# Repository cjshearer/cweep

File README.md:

## Overview

A compact, 34 key, solar powered, reversible, split keyboard.

<details>
  <summary>
    Schematic
  </summary>

</details>

## Case

The case is generated from `cweep.py` using CadQuery, with geometry extracted from user layers in `cweep.kicad_pcb`.

Generate case files to `case/`:

```sh
nix develop .#case --command python ~/repos/cweep/cweep.py
```

For interactive 3D viewing with live reloads:

```sh
nix develop .#case --command python ~/repos/cweep/cweep-dev.py
```

Changes to `cweep.py` or `cweep.kicad_pcb` automatically reload in the browser.

## Firmware

[*Generated by Shield Wizard for ZMK*](https://shield-wizard.genteure.workers.dev)

Reproducible builds with [Nix](https://nixos.org) thanks to [lilyinstarlight/zmk-nix](https://github.com/lilyinstarlight/zmk-nix):

```sh
# flash firmware with xiao dongle, resetting each board first
nix run .#flash reset reset reset dongle left right

# flash firmware with left as central, resetting each board first
nix run .#flash reset reset left_central right

# build all firmware and flash it yourself
nix build .#firmware
```

Builds in GitHub Actions coming soon.

## Bill of Materials (BOM)

| Description | Count | Value | Source |
|-------------|-------|-------|--------|
| Controller | 2 | [Seeed Xiao nRF52840](https://files.seeedstudio.com/wiki/XIAO/Seeed-Studio-XIAO-Series-SOM-Datasheet.pdf) | [Octopart](https://octopart.com/102010448-seeed+studio-126049022) |
| Controller Sockets | 4 | [310-43-107-41-001000](https://datasheet.octopart.com/310-43-107-41-001000-Mill-Max-datasheet-180673429.pdf) | [Octopart](https://octopart.com/310-43-107-41-001000-mill-max-657030) |
| Controller Pins | 28 | [3320-0-00-15-00-00-03-0](https://datasheet.octopart.com/3320-0-00-15-00-00-03-0-Mill-Max-datasheet-180682269.pdf) | [Octopart](https://octopart.com/3320-0-00-15-00-00-03-0-mill-max-29613931) |
| Battery/Reset Pogo Pins | 4 | [0906-0-15-20-76-14-11-0](https://datasheet.octopart.com/0906-0-15-20-76-14-11-0-Mill-Max-datasheet-180665642.pdf) | [Octopart](https://octopart.com/0906-0-15-20-76-14-11-0-mill-max-259418) |
| Battery | 2 | [ICR10440](https://www.powerstream.com/p/ICR10440-300mAh.pdf) | [Amazon](https://www.amazon.com/dp/B08H4RC1Y5) |
| Battery Contacts | 4 | [Keystone 230-1](https://docs.rs-online.com/a10d/0900766b8106e5ee.pdf) | [Octopart](https://octopart.com/230-1-keystone-154879) |
| Power Switch | 2 | [KAN-15](https://hackaday.io/project/174738-kan-15-led-tactile-switch/log/183418-switches-switches-switches#KAN-15:~:text=8016717020588253%26productId%3D4000960302909-,KAN%2D15,-Finally%2C%20I%20found) | [Amazon](https://us.amazon.com/dp/B0BHH2FBQ5) |
| Reset Button | 2 | [B3F-1020](https://omronfs.omron.com/en_US/ecb/products/pdf/en-b3f.pdf) (adafruit 367) | [Octopart](https://octopart.com/b3f-1020-omron-46944) |
| Kailh Choc V1 Keycaps | 34 | DDC Choc PBT Blanks | [Keebd](https://keebd.com/products/ddc-choc-pbt-blank-keycaps?variant=43210242785432) |
| Kailh Choc V1 Switches | 34 | [PG1350](https://cdn-shop.adafruit.com/product-files/5113/CHOC+keyswitch_Kailh-CPG135001D01_C400229.pdf) (e.g. [Sunset](https://cdn.shopify.com/s/files/1/0523/0847/6068/files/Choc_Sunset_datasheet.pdf))  | [Keebd](https://keebd.com/products/sunset-tactile-choc-switches?variant=41676091981976) |
| Kailh Choc Hotswap Sockets | 34 | [A5118](https://cdn-shop.adafruit.com/product-files/5118/5118-Choc-Socket.pdf) | [Octopart](https://octopart.com/5118-adafruit+industries-119967299) |
| Diodes | 34 | [1N4148W](https://datasheet.octopart.com/1N4148W-Diotec-datasheet-178941572.pdf) | [Octopart](https://octopart.com/1n4148w-diotec-42312312) |
| Solar Cell | 2 | [SM141K04LV](https://waf-e.dubudisk.com/anysolar.dubuplus.com/techsupport@anysolar.biz/O18Ae0B/DubuDisk/www/Gen3/SM141K04LV%20DATA%20SHEET%20202007.pdf) | [Octopart](https://octopart.com/sm141k04lv-anysolar-120091681) |
| Boost Converter | 2 | [BQ25504](https://www.ti.com/document-viewer/bq25504/datasheet) | [Octopart](https://octopart.com/bq25504rgtr-texas+instruments-20530455) |
| 4.7μF Capacitor (CHV1, CSTOR1) | 4 | [CL10A475KP8NNNC](https://datasheet.octopart.com/CL10A475KP8NNNC-Samsung-Electro-Mechanics-datasheet-11791968.pdf) | [Octopart](https://octopart.com/cl10a475kp8nnnc-samsung+electro-mechanics-9301844) |
| 10nF Capacitor (CREF1, CBYP1) | 4 | [C0603C103K5RACTU](https://octopart.com/c0603c103k5ractu-kemet-133094) | [Octopart](https://datasheet.octopart.com/C0603C103K5RACTU-Kemet-datasheet-11898999.pdf) |
| 22μH Inductor (LBST1) | 2 | [ASPI-4030S-220M-T](https://datasheet.octopart.com/ASPI-4030S-220M-T-Abracon-datasheet-27893147.pdf) | [Octopart](https://octopart.com/aspi-4030s-220m-t-abracon-29811505) |
| 4.42MΩ Resistor (ROV1) | 2 | [CRCW06034M42FKEA](https://datasheet.octopart.com/CRCW06034M42FKEA-Vishay-datasheet-175423584.pdf) | [Octopart](https://octopart.com/crcw06034m42fkea-vishay-39804278) |
| 5.49MΩ Resistor (ROV2) | 2 | [CRCW06035M49FKEA](https://datasheet.octopart.com/CRCW06035M49FKEA-Vishay-datasheet-175423584.pdf) | [Octopart](https://octopart.com/crcw06035m49fkea-vishay-39809097) |
| 3.83MΩ Resistor (RUV1, ROC2) | 4 | [CRCW06033M83FKEA](https://datasheet.octopart.com/CRCW06033M83FKEA-Vishay-datasheet-175423584.pdf) | [Octopart](https://octopart.com/crcw06033m83fkea-vishay-39857567) |
| 6.04MΩ Resistor (RUV2) | 2 | [CRCW06036M04FKEA](https://datasheet.octopart.com/CRCW06036M04FKEA-Vishay-datasheet-175423584.pdf) | [Octopart](https://octopart.com/crcw06036m04fkea-vishay-39816007) |
| 16MΩ Resistor (ROC1) | 2 | [RK73B1JTTDD166J](https://datasheet.octopart.com/RK73B1JTTDD166J-KOA-Speer-datasheet-182143539.pdf) | [Octopart](https://octopart.com/rk73b1jttdd166j-koa+speer-20075546) |
| 24AWG Stranded Silicone Wire | ~8in | N/A | [Amazon](https://www.amazon.com/dp/B01LH1G2IE) |

## Credits

This project is inspired by the work of many in the custom keyboard community:

- Pierre Chavalier's [Ferris](https://github.com/pierrechevalier83/ferris): for the original design and layout
- David Philip Barr's [Sweep](https://github.com/davidphilipbarr/Sweep/): inspiration to build a wireless, ferris-like keyboard using a daughter board for the microcontroller  
- GEIGEIGEIST's [TOTEM](https://github.com/GEIGEIGEIST/TOTEM): for it's excellent build guide, which helped me understand what types of components I may need for a wireless split keyboard
- Pete Johanson's [revxlp](https://gitlab.com/lpgalaxy/revxlp): for the usage and layout of pogo pins to connect a socketed Seeed Xiao's battery and reset pins to the PCB
- Xudongz's [Ergoblue](https://www.xudongz.com/blog/2020/ergoblue/): my initial inspiration for building a solar powered wireless keyboard
- NGuyen Vincent's [Aloidia](https://hackaday.io/project/189688-aloidia-wireless-split-solar-powered-keyboard): for the detailed build log and all-around excellent resource on building solar powered wireless keyboard

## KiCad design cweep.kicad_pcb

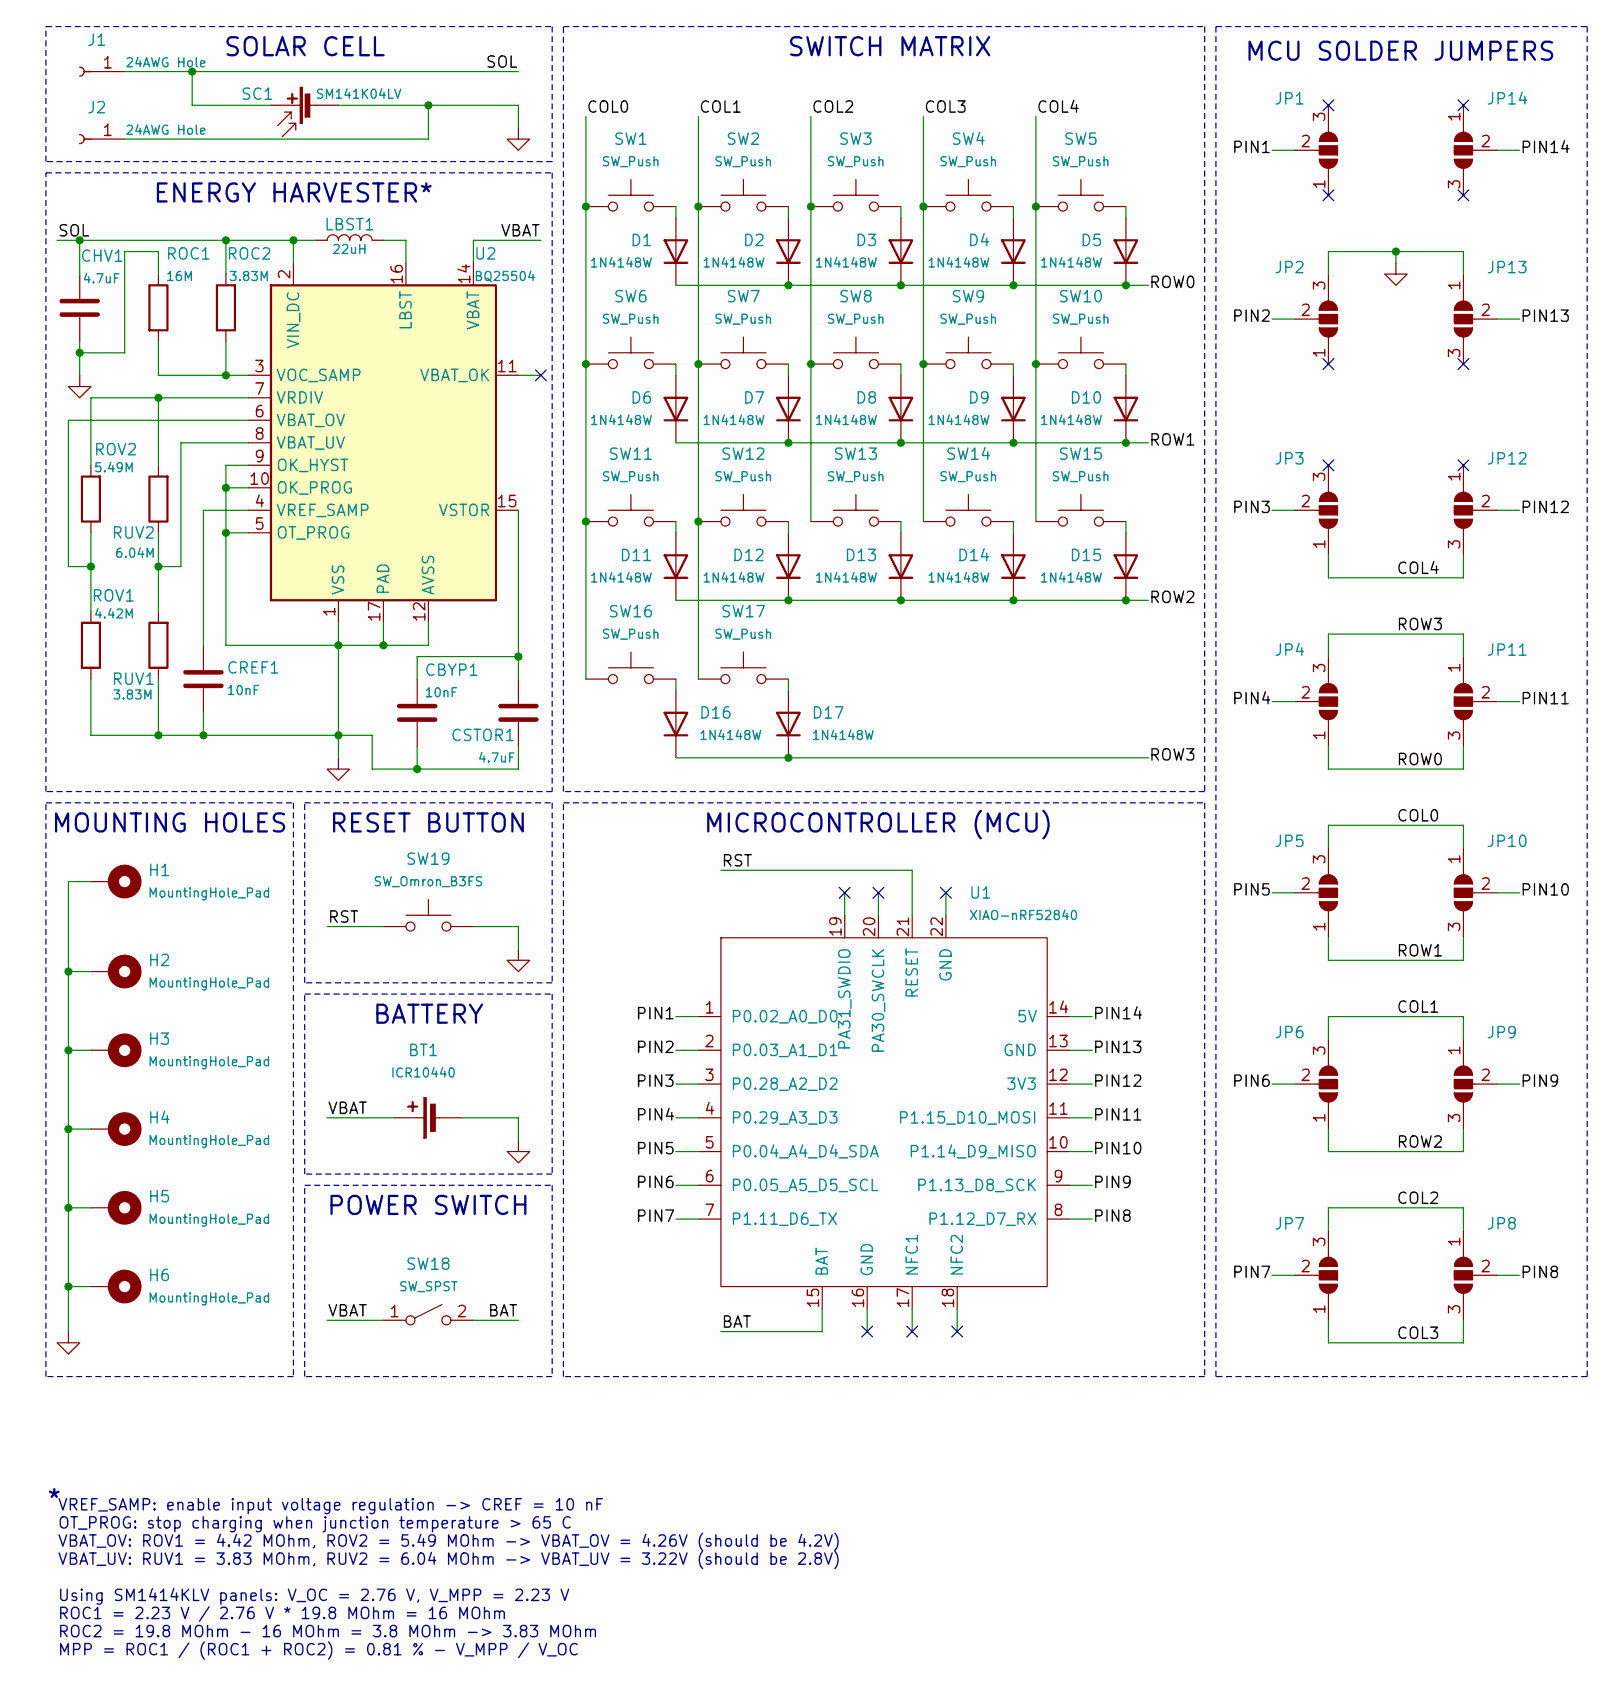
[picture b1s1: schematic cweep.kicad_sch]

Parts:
BT1: ICR10440; BatteryHolder_Keystone_230-1_1x10440
CBYP1: 10nF; C_0603_1608Metric_Pad1.08x0.95mm_HandSolder
CHV1: 4.7uF; C_0603_1608Metric_Pad1.08x0.95mm_HandSolder
CREF1: 10nF; C_0603_1608Metric_Pad1.08x0.95mm_HandSolder
CSTOR1: 4.7uF; C_0603_1608Metric_Pad1.08x0.95mm_HandSolder
D1, D2, D3, D4, D5, D6, D7, D8, D9, D10, D11, D12, D13, D14, D15, D16, D17: 1N4148W; D_SOD-123_Reversible
H1, H2, H3, H4, H5, H6: MountingHole_Pad; MountingHole_2.2mm_M2_DIN965_Pad
J1, J2: 24AWG Hole; SolderWire-0.127sqmm_1x01_D0.48mm_OD1mm_Relief
JP1, JP2, JP3, JP4, JP5, JP6, JP7, JP8, JP9, JP10, JP11, JP12, JP13, JP14: SolderJumper_3_Open; SolderJumper-3_P2.0mm_Open_TrianglePad1.0x1.5mm_Reversible
LBST1: 22uH; L_Abracon_ASPI-4030S_Reversible
ROC1: 16M; R_0603_1608Metric_Pad0.98x0.95mm_HandSolder
ROC2: 3.83M; R_0603_1608Metric_Pad0.98x0.95mm_HandSolder
ROV1: 4.42M; R_0603_1608Metric_Pad0.98x0.95mm_HandSolder
ROV2: 5.49M; R_0603_1608Metric_Pad0.98x0.95mm_HandSolder
RUV1: 3.83M; R_0603_1608Metric_Pad0.98x0.95mm_HandSolder
RUV2: 6.04M; R_0603_1608Metric_Pad0.98x0.95mm_HandSolder
SC1: SM141K04LV
SW1, SW2, SW3, SW4, SW5, SW6, SW7, SW8, SW9, SW10, SW11, SW12, SW13, SW14, SW15, SW16, SW17: SW_Push; SW_Hotswap_Kailh_Choc_V1_1.00u_Reversible
SW18: SW_SPST; SW_KAN-15_PHT_Reversible
SW19: SW_Omron_B3FS; SW_TH_Tactile_Omron_B3F-102x_Reversible
U1: XIAO-nRF52840; XIAO-nRF52840_Reversible
U2: BQ25504; VQFN-16-1EP_3x3mm_P0.5mm_EP1.68x1.68mm

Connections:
/BAT: SW18.2 (B), U1.15 (BAT)
/COL0: JP5.3 (B), JP10.1 (A), SW1.1, SW6.1, SW11.1, SW16.1
/COL1: JP6.3 (B), JP9.1 (A), SW2.1, SW7.1, SW12.1, SW17.1
/COL2: JP7.3 (B), JP8.1 (A), SW3.1, SW8.1, SW13.1
/COL3: JP7.1 (A), JP8.3 (B), SW4.1, SW9.1, SW14.1
/COL4: JP3.1 (A), JP12.3 (B), SW5.1, SW10.1, SW15.1
/PIN1: JP1.2 (C), U1.1 (P0.02_A0_D0)
/PIN2: JP2.2 (C), U1.2 (P0.03_A1_D1)
/PIN3: JP3.2 (C), U1.3 (P0.28_A2_D2)
/PIN4: JP4.2 (C), U1.4 (P0.29_A3_D3)
/PIN5: JP5.2 (C), U1.5 (P0.04_A4_D4_SDA)
/PIN6: JP6.2 (C), U1.6 (P0.05_A5_D5_SCL)
/PIN7: JP7.2 (C), U1.7 (P1.11_D6_TX)
/PIN8: JP8.2 (C), U1.8 (P1.12_D7_RX)
/PIN9: JP9.2 (C), U1.9 (P1.13_D8_SCK)
/PIN10: JP10.2 (C), U1.10 (P1.14_D9_MISO)
/PIN11: JP11.2 (C), U1.11 (P1.15_D10_MOSI)
/PIN12: JP12.2 (C), U1.12 (3V3)
/PIN13: JP13.2 (C), U1.13 (GND)
/PIN14: JP14.2 (C), U1.14 (5V)
/ROW0: D1.1 (K), D2.1 (K), D3.1 (K), D4.1 (K), D5.1 (K), JP4.1 (A), JP11.3 (B)
/ROW1: D6.1 (K), D7.1 (K), D8.1 (K), D9.1 (K), D10.1 (K), JP5.1 (A), JP10.3 (B)
/ROW2: D11.1 (K), D12.1 (K), D13.1 (K), D14.1 (K), D15.1 (K), JP6.1 (A), JP9.3 (B)
/ROW3: D16.1 (K), D17.1 (K), JP4.3 (B), JP11.1 (A)
/RST: SW19.1, U1.21 (RESET)
/SOL: CHV1.1, J1.1, LBST1.1, ROC2.2, SC1.1 (+), U2.2 (VIN_DC)
/VBAT: BT1.1 (+), SW18.1 (A), U2.14 (VBAT)
GND: BT1.2 (-), CBYP1.2, CHV1.2, CREF1.2, CSTOR1.2, H1.1, H2.1, H3.1, H4.1, H5.1, H6.1, J2.1, JP2.3 (B), JP13.1 (A), ROC1.1, ROV1.1, RUV1.1, SC1.2 (-), SW19.2, U2.1 (VSS), U2.5 (OT_PROG), U2.9 (OK_HYST), U2.10 (OK_PROG), U2.12 (AVSS), U2.13 (VSS), U2.17 (PAD)
unnamed: D1.2 (A), SW1.2
unnamed: D2.2 (A), SW2.2
unnamed: D3.2 (A), SW3.2
unnamed: D4.2 (A), SW4.2
unnamed: D5.2 (A), SW5.2
unnamed: D6.2 (A), SW6.2
unnamed: D7.2 (A), SW7.2
unnamed: D8.2 (A), SW8.2
unnamed: D9.2 (A), SW9.2
unnamed: D10.2 (A), SW10.2
unnamed: D11.2 (A), SW11.2
unnamed: D12.2 (A), SW12.2
unnamed: D13.2 (A), SW13.2
unnamed: D14.2 (A), SW14.2
unnamed: D15.2 (A), SW15.2
unnamed: D16.2 (A), SW16.2
unnamed: D17.2 (A), SW17.2
unnamed: LBST1.2, U2.16 (LBST)
unnamed: ROV1.2, ROV2.1, U2.6 (VBAT_OV)
unnamed: RUV1.2, RUV2.1, U2.8 (VBAT_UV)
unnamed: ROC1.2, ROC2.1, U2.3 (VOC_SAMP)
unnamed: ROV2.2, RUV2.2, U2.7 (VRDIV)
unnamed: CREF1.1, U2.4 (VREF_SAMP)
unnamed: CBYP1.1, CSTOR1.1, U2.15 (VSTOR)

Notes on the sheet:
MCU SOLDER JUMPERS
VREF_SAMP: enable input voltage regulation -> CREF = 10 nF OT_PROG: stop charging when junction temperature > 65 C VBAT_OV: ROV1 = 4.42 MOhm, ROV2 = 5.49 MOhm -> VBAT_OV = 4.26V (should be 4.2V) VBAT_UV: RUV1 = 3.83 MOhm, RUV2 = 6.04 MOhm -> VBAT_UV = 3.22V (should be 2.8V) Using SM1414KLV panels: 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
BATTERY
ENERGY HARVESTER*
SWITCH MATRIX
RESET BUTTON
MICROCONTROLLER (MCU)
POWER SWITCH
SOLAR CELL
MOUNTING HOLES

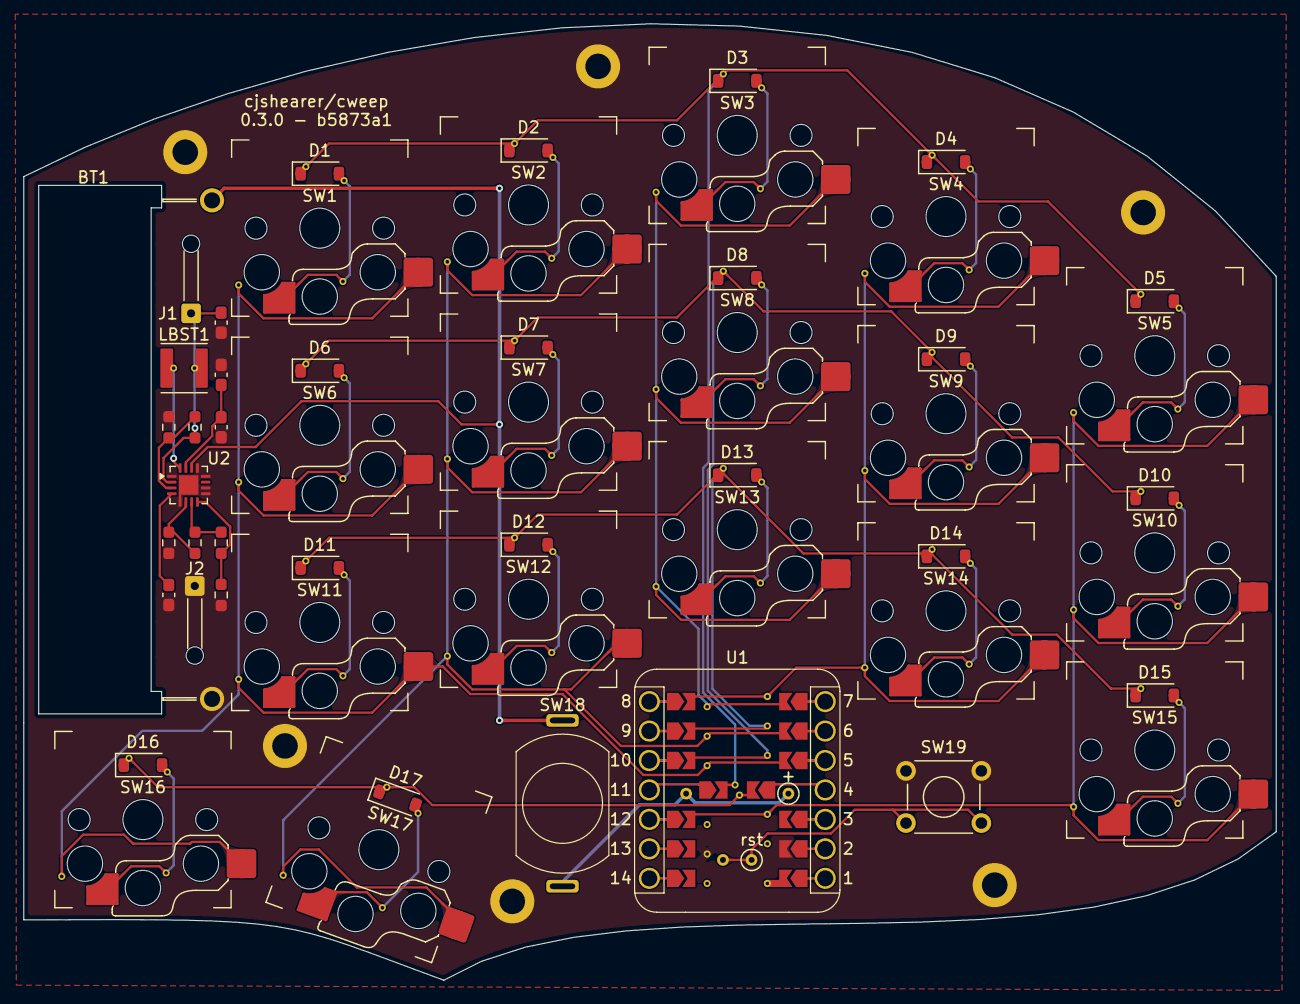
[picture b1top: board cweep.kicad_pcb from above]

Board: 2 copper layers, 108.0 x 82.5 mm, 73 parts (1 on the bottom side), 52 nets.

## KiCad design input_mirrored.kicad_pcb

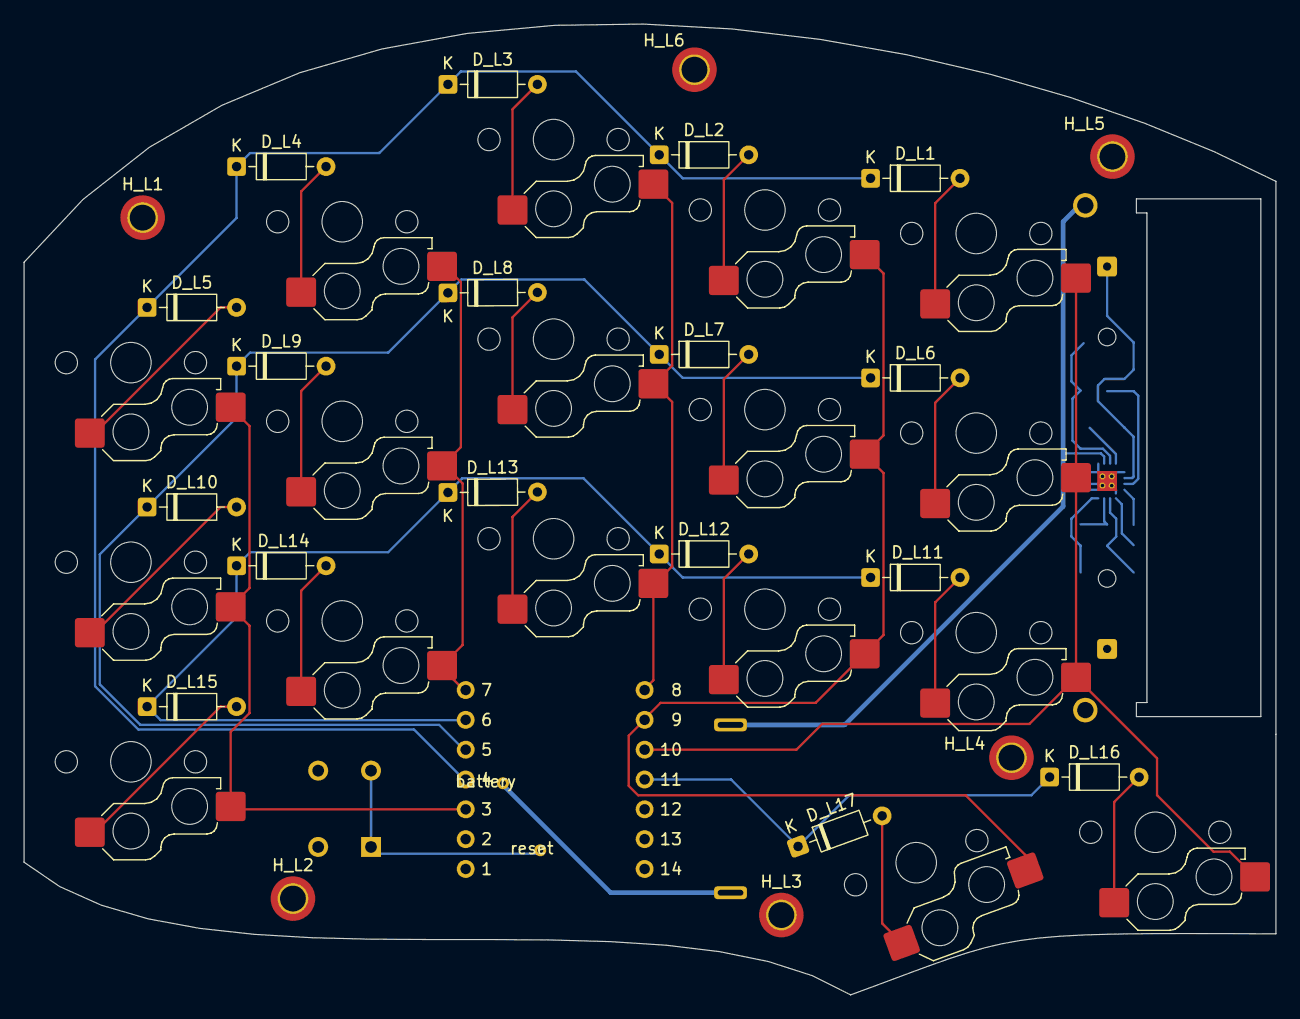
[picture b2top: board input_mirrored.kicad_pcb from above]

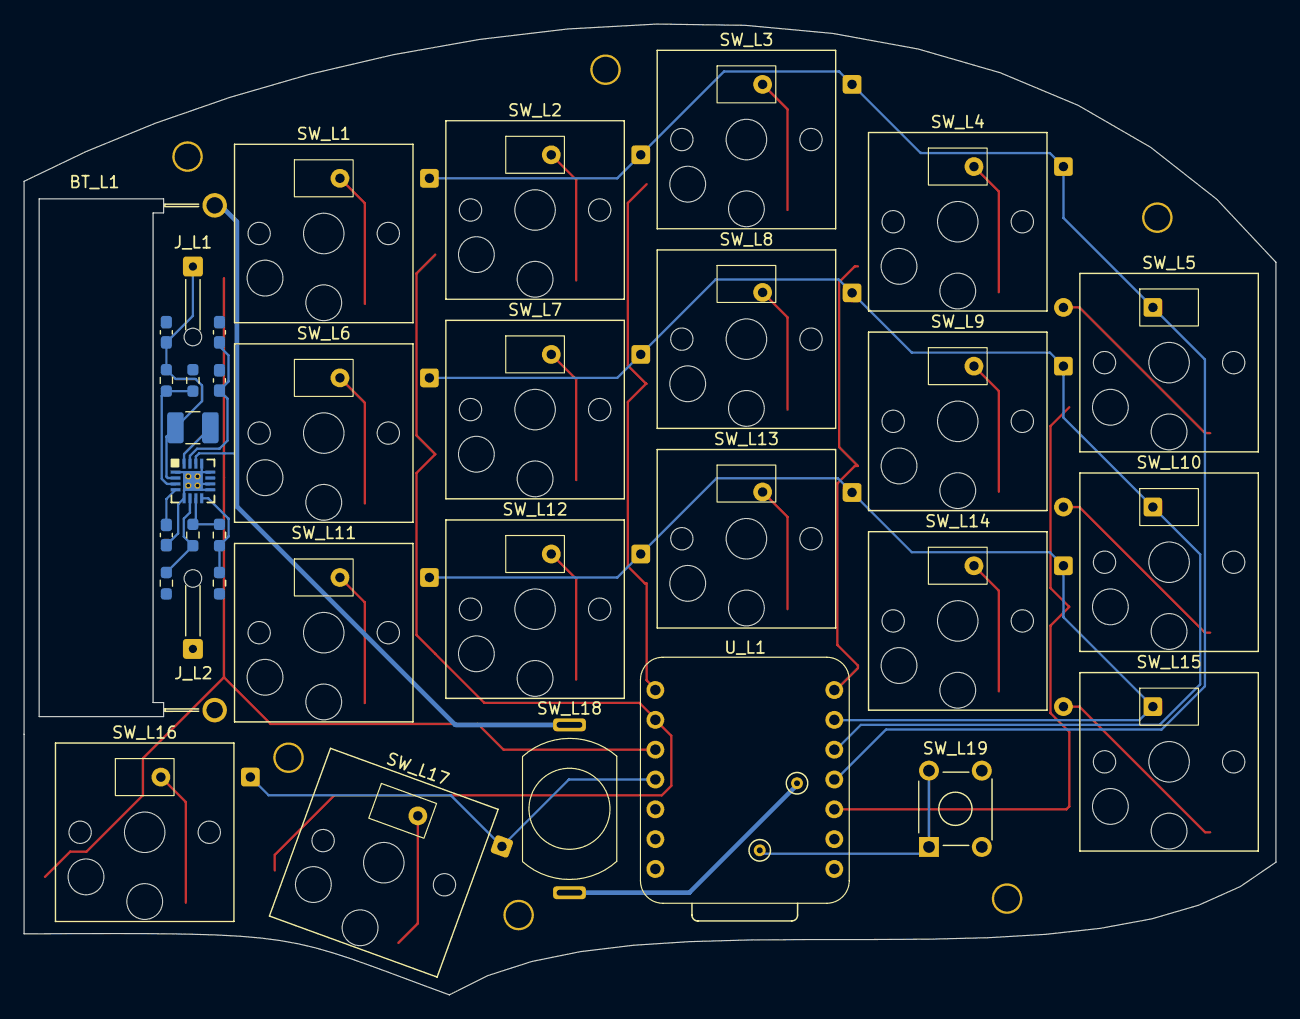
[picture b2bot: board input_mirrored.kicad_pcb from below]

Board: 2 copper layers, 106.6 x 82.7 mm, 59 parts (36 on the bottom side), 38 nets.

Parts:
BT_L1: 10440; BatteryHolder_Keystone_230-1_1x10440
CBYP_L1: 10nF; C_0603_1608Metric_Pad1.08x0.95mm_HandSolder
CHV_L1: 4.7uF; C_0603_1608Metric_Pad1.08x0.95mm_HandSolder
CREF_L1: 10nF; C_0603_1608Metric_Pad1.08x0.95mm_HandSolder
CSTOR_L1: 4.7uF; C_0603_1608Metric_Pad1.08x0.95mm_HandSolder
D_L1, D_L2, D_L3, D_L4, D_L5, D_L6, D_L7, D_L8, D_L9, D_L10, D_L11, D_L12, D_L13, D_L14, D_L15, D_L16, D_L17: 1N4148; D_DO-35_SOD27_P7.62mm_Horizontal
H_L1, H_L2, H_L3, H_L4, H_L5, H_L6: MountingHole_Pad; MountingHole_2.2mm_M2_DIN965_Pad_TopOnly
J_L1, J_L2: 24AWG Hole; SolderWire-0.127sqmm_1x01_D0.48mm_OD1mm_Relief
LBST_L1: 22uH; L_1210_3225Metric_Pad1.42x2.65mm_HandSolder
ROC_L1: 16M; R_0603_1608Metric_Pad0.98x0.95mm_HandSolder
ROC_L2: 3.83M; R_0603_1608Metric_Pad0.98x0.95mm_HandSolder
ROV_L1: 4.42M; R_0603_1608Metric_Pad0.98x0.95mm_HandSolder
ROV_L2: 5.49M; R_0603_1608Metric_Pad0.98x0.95mm_HandSolder
RUV_L1: 3.83M; R_0603_1608Metric_Pad0.98x0.95mm_HandSolder
RUV_L2: 6.04M; R_0603_1608Metric_Pad0.98x0.95mm_HandSolder
SC_L1: SM141K04LV
SW_L1, SW_L2, SW_L3, SW_L4, SW_L5, SW_L6, SW_L7, SW_L8, SW_L9, SW_L10, SW_L11, SW_L12, SW_L13, SW_L14, SW_L15, SW_L16, SW_L17: SW_Push; SW_Hotswap_Kailh_Choc_V1_1.00u
SW_L18: SW_SPST; SW_KAN-15_PHT
SW_L19: SW_Omron_B3FS; SW_TH_Tactile_Omron_B3F-10xx
U_L1: XIAO-nRF52840
U_L2: BQ25504RGTR; RGT16_1P7X1P7

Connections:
/BAT_R: SW_L18.2 (B), U_L1.15 (BAT)
/COL_L0: SW_L1.1, SW_L6.1, SW_L11.1, SW_L16.1, U_L1.10 (P1.14_D9_MISO)
/COL_L1: SW_L2.1, SW_L7.1, SW_L12.1, SW_L17.1, U_L1.9 (P1.13_D8_SCK)
/COL_L2: SW_L3.1, SW_L8.1, SW_L13.1, U_L1.8 (P1.12_D7_RX)
/COL_L3: SW_L4.1, SW_L9.1, SW_L14.1, U_L1.7 (P1.11_D6_TX)
/COL_L4: SW_L5.1, SW_L10.1, SW_L15.1, U_L1.3 (P0.28_A2_D2)
/ROW_L0: D_L1.1 (K), D_L2.1 (K), D_L3.1 (K), D_L4.1 (K), D_L5.1 (K), U_L1.4 (P0.29_A3_D3)
/ROW_L1: D_L6.1 (K), D_L7.1 (K), D_L8.1 (K), D_L9.1 (K), D_L10.1 (K), U_L1.5 (P0.04_A4_D4_SDA)
/ROW_L2: D_L11.1 (K), D_L12.1 (K), D_L13.1 (K), D_L14.1 (K), D_L15.1 (K), U_L1.6 (P0.05_A5_D5_SCL)
/ROW_L3: D_L16.1 (K), D_L17.1 (K), U_L1.11 (P1.15_D10_MOSI)
/RST_R: SW_L19.1, U_L1.21 (RESET)
/SOL_R: CHV_L1.1, J_L1.1, LBST_L1.1, ROC_L2.2, U_L2.2 (VIN_DC)
/VBAT_R: BT_L1.1 (+), SW_L18.1 (A), U_L2.14 (VBAT)
GND: BT_L1.2 (-), CBYP_L1.2, CHV_L1.2, CREF_L1.2, CSTOR_L1.2, H_L1.1, H_L2.1, H_L3.1, H_L4.1, H_L5.1, H_L6.1, J_L2.1, ROC_L1.1, ROV_L1.1, RUV_L1.1, SW_L19.2, U_L1.13 (GND), U_L2.1 (VSS), U_L2.5 (OT_PROG), U_L2.9 (OK_HYST), U_L2.10 (OK_PROG), U_L2.12 (AVSS), U_L2.13 (VSS), U_L2.17 (EPAD)
unnamed: D_L1.2 (A), SW_L1.2
unnamed: D_L2.2 (A), SW_L2.2
unnamed: D_L3.2 (A), SW_L3.2
unnamed: D_L4.2 (A), SW_L4.2
unnamed: D_L5.2 (A), SW_L5.2
unnamed: D_L6.2 (A), SW_L6.2
unnamed: D_L7.2 (A), SW_L7.2
unnamed: D_L8.2 (A), SW_L8.2
unnamed: D_L9.2 (A), SW_L9.2
unnamed: D_L10.2 (A), SW_L10.2
unnamed: D_L11.2 (A), SW_L11.2
unnamed: D_L12.2 (A), SW_L12.2
unnamed: D_L13.2 (A), SW_L13.2
unnamed: D_L14.2 (A), SW_L14.2
unnamed: D_L15.2 (A), SW_L15.2
unnamed: D_L16.2 (A), SW_L16.2
unnamed: D_L17.2 (A), SW_L17.2
unnamed: LBST_L1.2, U_L2.16 (LBST)
unnamed: ROV_L1.2, ROV_L2.1, U_L2.6 (VBAT_OV)
unnamed: RUV_L1.2, RUV_L2.1, U_L2.8 (VBAT_UV)
unnamed: ROC_L1.2, ROC_L2.1, U_L2.3 (VOC_SAMP)
unnamed: ROV_L2.2, RUV_L2.2, U_L2.7 (VRDIV)
unnamed: CREF_L1.1, U_L2.4 (VREF_SAMP)
unnamed: CBYP_L1.1, CSTOR_L1.1, U_L2.15 (VSTOR)

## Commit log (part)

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2025-05-03 init
2025-05-03 refactor: flatten directory structure
2025-05-03 feat: add MCU battery pogo pin
2025-05-03 refactor: vendor assets
2025-05-03 refactor: add gitignore
2025-05-03 feat: add matrix wiring
2025-05-03 feat: add MCU reset pogo pin
2025-05-03 fix: mark unused pins
2025-05-03 refactor: update footprints
2025-05-05 feat: add matrix-to-mcu routes
2025-05-20 feat: add solar charging circuit
2025-05-20 feat: add solar footprint and models
2025-05-25 feat: add battery
2025-05-26 feat: add matrix traces
2025-05-26 fix: placement for key-cap tolerances
2025-05-27 refactor: shorten column 0 trace
2025-05-28 docs: update bill-of-materials and todos
2025-05-31 refactor: remove unused no-connect
2025-05-31 feat: add battery cutout
2025-05-31 feat: add battery jst header
2025-06-01 feat: add edge cuts
2025-06-01 refactor: reveal keycaps
2025-06-01 refactor: fix solar cell appearance
2025-06-07 fix: remove unused paste
2025-06-07 refactor: add plot settings
2025-06-08 docs: add images
2025-06-08 docs: fix image alignment
2025-06-13 docs: make schematic and pcb images easily opened in new window
2025-06-21 fix: avoid text clipping
2025-06-21 fix: add missing switch track
2025-06-21 docs: add solar cell data sheet
2025-06-21 docs: update images
2025-06-22 refactor: shorten row trace
2025-07-27 feat: add reset button and power switch
2025-08-01 fix: reorganize parts for better fit
2025-08-03 feat: battery capacity 110mAh -> 350mAh
2025-08-05 fix: remove unused pogo pins from solar cell
2025-08-05 fix: battery connector spacing
2025-08-06 docs: fix image links
2025-08-06 docs: fix image link
2025-08-07 fix: align reset switch with power switch
2025-08-08 fix: re-attach traces for gpio, power, and reset switches
2025-08-09 refactor: improve traces routing
2025-08-09 feat: add case mounting holes
2025-08-09 feat: 2.5mm -> 2.2mm mounting holes
2025-08-09 fix: join solar ground zone and avoid silkscreen clipping
2025-08-10 fix: add missing B3F-102x model
    The model is broken and will be until
    https://gitlab.com/kicad/libraries/kicad-packages3D/-/merge_requests/1239
    lands.
2025-08-10 refactor: add solar cell contact labels
2025-08-10 docs: reorder images
2025-08-10 fix: solar cell contact radius
2025-08-15 feat: add solar cell connectors
2025-08-15 fix: AAA -> 10440
2025-08-17 refactor: normalize labels and organize schematic
2025-09-09 feat: make keyboard switch reversible
    * fix: use SMD diode to accommodate reversible switch
2025-09-09 feat: make remaining components reversible
2025-09-09 refactor: use kicad libraries for BQ25504
2025-09-09 fix: solar cell placement
2025-09-09 fix: increase battery cutout
    I increased the size of the battery cutout to
    ensure the battery clips fit in the cutout. I left
    the battery clips where they were, since they are
    42.99mm apart, which is 1mm less than what the
    datasheet recommends for a AAA battery. However,
    the 10440 battery I will be using is 1mm smaller
2025-09-09 fix: move capacitors nearer BQ25504
    The layout guidelines for the BQ25504 recommend
    placing the output capacitors as close as possible
    to the IC, followed by the input capacitors, and
    finally the inductor.
    Previously, I had this backwards, but with this
    commit the components are now in the recommended
2025-09-09 fix: xiao silkscreen
    The silkscreen for the reversible xiao footprint
    was confusing, so I updated it to be more clear.
2025-09-13 docs: change CREF1 capacitor
2025-09-13 refactor: 10440 -> ICR10440
2025-09-17 fix: correct footprint for inductor
2025-09-18 docs: add remaining components to BOM
2025-09-18 docs: update status
2025-09-19 fix: remove unused zone exclusion
2025-09-19 feat: add script to generate images
2025-09-20 docs: note that it's reversible
2025-09-20 docs: add 24AWG wire
2025-09-20 refactor: satisfy shellcheck
2025-09-20 refactor: ignore generated images
2025-09-20 fix: image generation
2025-09-20 fix: release script doesn't duplicate anchor
2025-09-20 docs: update KAN-15 with active source
2025-09-21 fix: replace socket with on normally in stock
2025-09-21 refactor: replace socket with cheaper alternative
2025-09-21 build: 0.1.0 -> 0.2.0
2025-09-21 docs: fix wrong image src
2025-09-21 refactor: dedup part for RUV1 and ROC2
2025-09-25 fix: add missing battery contacts
2025-10-04 feat: add direnv
2025-10-05 fix: halves connect to dongle
    The keyboard halves were not connecting to the
    dongle, as the left half would always behave as
    the central.
    This commit splits the builds for each firmware,
    such that `-DCONFIG_ZMK_SPLIT_ROLE_CENTRAL=n` can
    be set for the left half.
2025-10-08 feat: add cweep keymap
2025-10-19 fix: don't overlap jumper pad and rst courtyards
2025-10-19 docs: shorten link for 24AWG wire
2025-10-19 docs: add release notes
2025-10-19 feat: annotate hotswap kailh choc for case generation
    To generate the case for each side of the
    keyboard, I will be annotating the footprint and
    placement of each physical component with F.Right,
    B.Right, F.Left, or B.Left (User.1 through
    User.4).
    In this commit, I have annotated the hotswap kailh
2025-10-19 feat: annotate power switch for case generation
2025-10-22 fix: use accurate kailh choc CPG135001S30 socket
    There were no high quality footprints for the
    Kailh Choc hotswap sockets, so I created one based
    on the original line art from the datasheet to
    improve accuracy.
2025-10-22 fix: power switch overlapping courtyard
2025-11-23 feat: add reset switch cutouts and model paths
2025-11-23 refactor: swap wrl for stp
    STEP exports better for use in OpenScad.
2025-11-23 feat: add solder wire cutouts
2025-11-23 fix: remove small walls from switch cutouts
2025-11-23 feat: add xiao bottom cutouts
2025-11-27 feat: add solar circuit cutouts
2025-11-27 fix: correct user layer assignments for front and back
2025-11-27 refactor: join right and left annotations
    Consolidate left/right cutout annotations into
    unified front/back layers. Prepare for future use
    of freed layers for fill regions.
2025-12-20 feat: add case build scripts
2025-12-26 fix: reload openscad preview
2025-12-26 refactor: remove unused fill for choc switches
2025-12-28 fix: cutout kailh hotswap contact
2025-12-30 fix: close excess battery cutout for bottom plate
2025-12-30 feat: add threaded M2 DIN 965 cutout to bottom plate
2026-01-03 refactor: build plates from just bottom and top plate
2026-02-17 refactor: replace some polygons with rectangles
2026-02-22 fix: close cutout for omron switch
2026-02-25 fix: close cutout for kailh choc sockets
2026-03-01 fix: heal degenerate bezier in hotswap footprint
    The hotswap footprint had two cubic Bézier
    segments with coincident control points (Curve
    209: P0=P1, Curve 210: P2=P3), which creates
    zero-length endpoint tangents. That degenerate
    geometry causes OCCT/CadQuery offset2D to fail
    with "Null TopoDS_Shape" when generating User.5
2026-03-15 fix: remove small unnecessary cutout for omron
2026-03-15 fix: simplify kailh switch cutout
2026-03-18 fix: lower kailh switch model onto pcb
2026-03-20 fix: align keycap model with switch
2026-04-25 fix: align xiao and its pads
2026-04-25 build: 0.2.1 -> 0.3.0
2026-05-02 fix: enlarge solder wire top plate cutouts
2026-05-02 refactor: add empty SolarTop layer
    Insert a new empty User.1 "F.Plate.SolarTop" layer in the board layer
    table and shift the remaining User layers up by one, renaming them as
    they move:
    User.1 F.Plate.Solar -> User.2 F.Plate.SolarWall
    User.2 F.Plate.Cover -> User.3 F.Plate.Cover
    User.3 F.Plate.Switch -> User.4 F.Plate.Switch
2026-05-02 fix: raise battery model to match reality
    The battery doesn't sit perfectly in the notch cut for it, so we raise
    it up by 0.37mm, up from 6.53mm from top of pcb to top of battery to
    6.9mm.
2026-05-02 refactor: replace openscad with cadquery
2026-05-09 feat: add solar battery compartment
    Add a compartment that houses the battery and provides a mounting point
    for the solar cell.
    The battery holder's plate cutouts are widened so the battery sits in a
    rounded recess, and the solar cell footprint is moved into its new
    position. New SolarTop/SolarWall plate outlines plus a few
    spacer/switch/cover items are drawn on the board, and the script now
2026-05-11 refactor: use shared tolerance
2026-05-15 refactor: skip PCB model generation if unchanged
    cweep-dev.py only re-exports the PCB assembly STEP when it is missing
    or older than the PCB file, avoiding a slow kicad-cli run on every
    reload of the viewer.
2026-05-15 feat: add solar battery compartment
    This commit adds a compartment that both houses
    the battery and provides a mounting point for the
    solar cell.
    The compartment features a rounded cutout for the
    battery, which doubles as a support rib for face
    that the solar cell is mounted on. It also has a
2026-05-16 feat: visualize screws and threaded inserts
2026-05-16 feat: visualize screws and threaded inserts
    Import 3D models of the M2 flat-head screw and the heat-set threaded
    insert, and instance them at every mounting hole in the --preview
    viewer so the hardware fitment can be checked at a glance. The models
    live in 3dmodels/.
2026-05-23 refactor: derive cutouts from footprint placements
    Track each feature's footprint placements (angle + offset) and build
    the plate cutouts from procedural wires placed at those locations
    instead of drawing them on User layers: kailh shallow/mid/deep cuts,
    battery holder top, inductor/capacitor/resistor/power-IC spacer rects,
    reset button, solder wires, MCU cover and side rails, and the power
    switch.
2026-05-24 refactor: build cutouts as per-feature 3D solids
    Move from "cut profiles at footprint locations" to "build one cutout
    solid per feature, then transform it to each placement and subtract".
    Each feature gets a build_top_cutout/build_bottom_cutout pair; the
    kailh switches reconstruct their bottom socket from F.Fab/B.Fab/drill
    local wires, and the board cutout becomes a body-with-tabs extrusion.
    All User layer usage is gone from the script at this point.
2026-05-25 build: update flake inputs
    Refresh the flake lock and bump the local python module versions:
    - cadquery-ocp 7.8.1.2 -> 7.9.3.1.1 (release stubs are now named "Linux")
    - cadquery 2.7.0 -> 8c17892 (development revision)
    - ocp-tessellate 3.2.2 -> 3.3.0
    - ocp-vscode 3.3.4 -> 3.4.0
    - threejs-materials 1.0.4 -> 1.1.1
2026-05-25 refactor: extract kicad geometry as sketches
    Extract PCB geometry directly into cadquery sketches instead of going
    through edges and wires. add_item_to_sketch converts each KiCad
    graphic item into the matching sketch primitive
    (segment/bezier/polygon/arc/rect/circle) and finalize_raw_sketch
    assembles faces from the sketch edges, keeping
    feature_sketch[feature][layer] as sketch objects. Pads and drills are
2026-05-26 refactor: cut per stage instead of per span
    The span-based pipeline was slow and its combined profiles hard to
    debug, so replace it with a per-stage loop: placements are grouped by
    angle and each feature stage is cut with one combined placed sketch.
    Restore the battery holder, kailh switches (bottom reconstructed from
    F.Fab/B.Fab/drill), inductors, capacitors, resistors, power IC, reset
    button, solder wires and power switch stages. A
2026-06-03 refactor: drive construction from feature_stages
    Move all construction into a feature_stages dictionary: each feature
    carries its placements and a set of named stages, each stage a sketch
    plus operations ({target, kind: union|cut, start, end, offset, apply})
    applied against the plate solids via a tagged base workplane. The
    plate shells and the solar component are expressed as features too,
    replacing the build_top_solar_component function.
2026-06-07 fix: align surface normals of extracted geometry
    After the KiCad Y-axis flip, the assembled sketch faces ended up wound
    backwards. Traverse the directional primitives in reverse (segments
    end->start, reversed bezier/polygon coordinates, arcs end->mid->start)
    so the faces keep their normals pointing up.
